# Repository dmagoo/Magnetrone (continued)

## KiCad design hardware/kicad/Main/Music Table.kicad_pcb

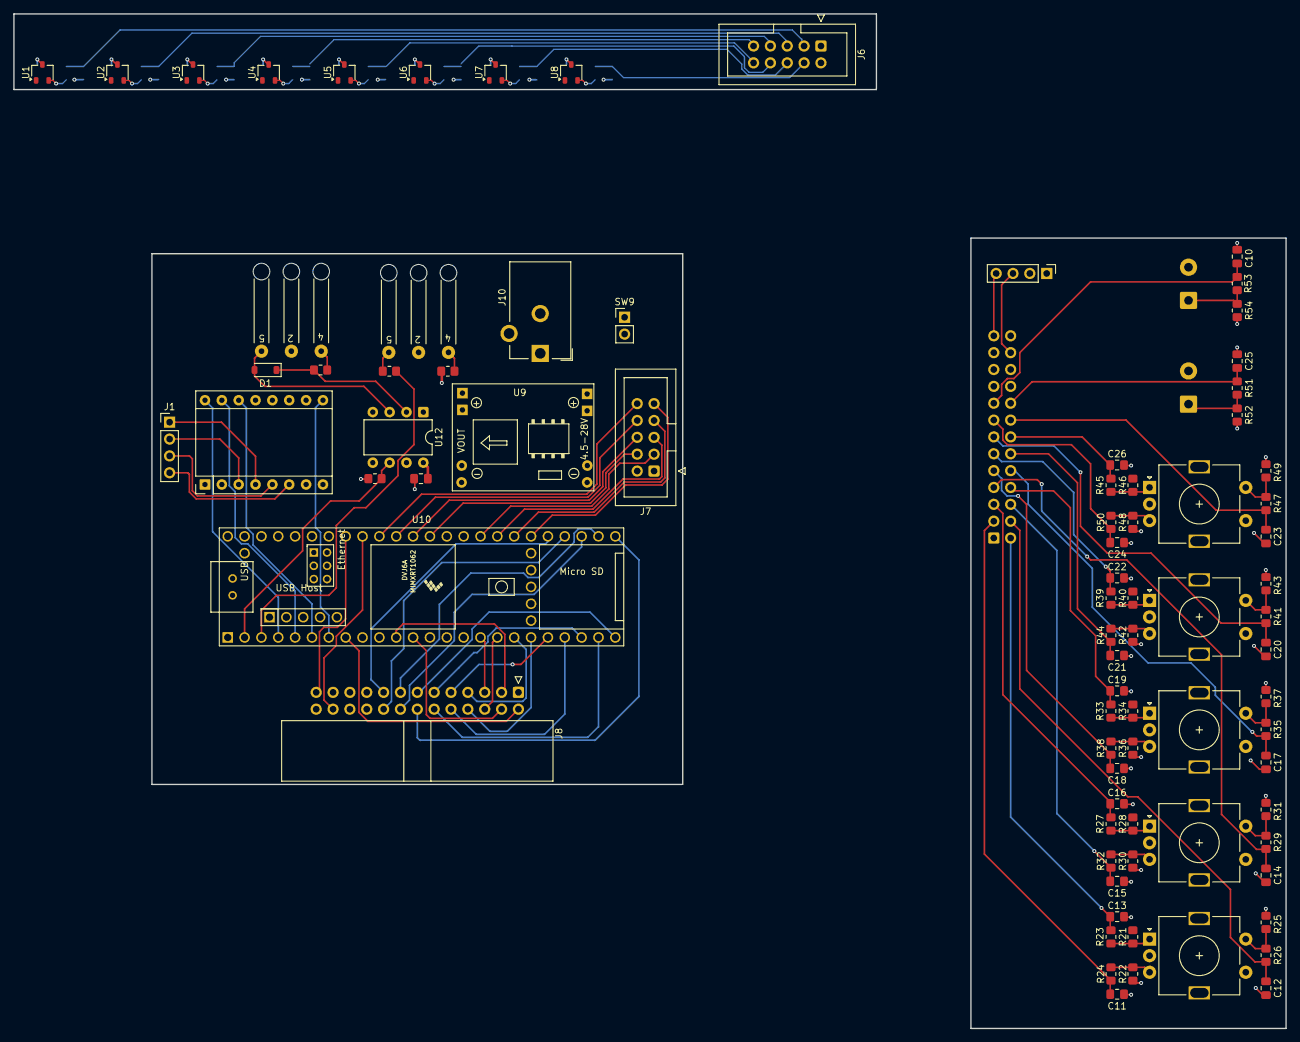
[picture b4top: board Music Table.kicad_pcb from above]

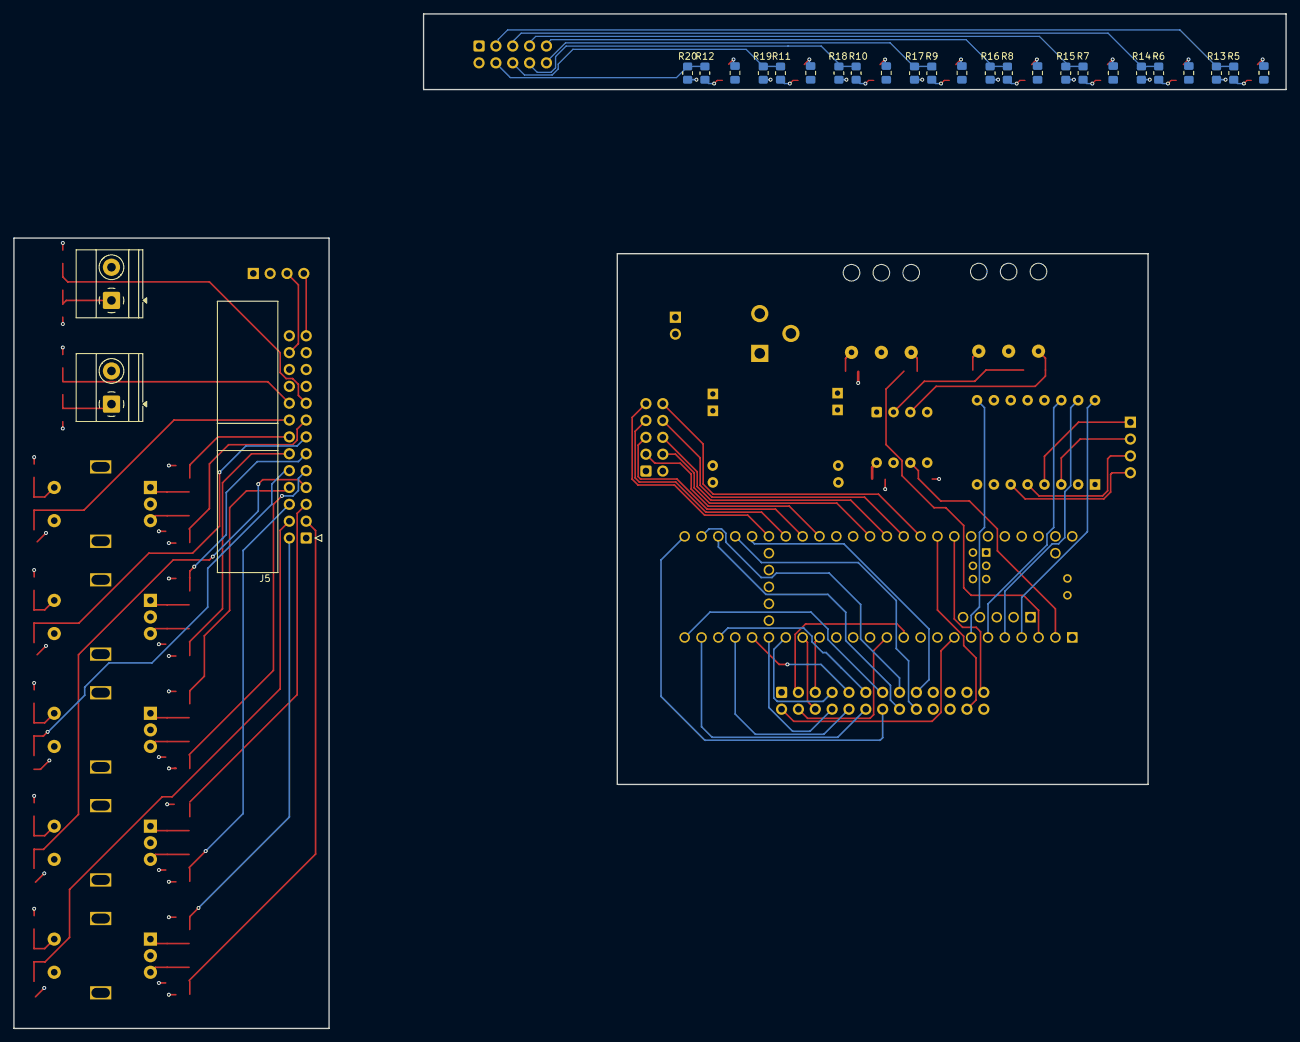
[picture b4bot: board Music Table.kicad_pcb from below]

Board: 4 copper layers, 191.7 x 152.9 mm, 110 parts (27 on the bottom side), 98 nets.

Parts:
A1: Pololu_Breakout_A4988; Pololu_Breakout-16_15.2x20.3mm
C1, C2, C3, C4, C5, C6, C7, C8, C9: .1uf; C_0805_2012Metric_Pad1.18x1.45mm_HandSolder
C10, C25: C; C_0805_2012Metric_Pad1.18x1.45mm_HandSolder
C11, C12, C13, C14, C15, C16, C17, C18, C19, C20, C21, C22, C23, C24, C26: .01uf; C_0805_2012Metric_Pad1.18x1.45mm_HandSolder
D1: D; D_SOD-123
J1, J9: Conn_01x04; PinHeader_1x04_P2.54mm_Vertical
J2, J3: DIN-5_180degree; MIDI_Wire_245
J5, J8: Conn_02x13_Counter_Clockwise; IDC-Header_2x13_P2.54mm_Horizontal
J6, J7: Conn_02x05_Odd_Even; IDC-Header_2x05_P2.54mm_Vertical
J10: Barrel_Jack; BarrelJack_CUI_PJ-102AH_Horizontal
R1, R2, R3: 220; R_0805_2012Metric_Pad1.20x1.40mm_HandSolder
R4: 470k; R_0805_2012Metric_Pad1.20x1.40mm_HandSolder
R5, R6, R7, R8, R9, R10, R11, R12: 10000; R_0805_2012Metric_Pad1.20x1.40mm_HandSolder
R13, R14, R15, R16, R17, R18, R19, R20: 20000; R_0805_2012Metric_Pad1.20x1.40mm_HandSolder
R21, R22, R23, R24, R25, R26, R27, R28, R29, R30, R31, R32, R33, R34, R35, R36, R37, R38, R39, R40, R41, R42, R43, R44, R45, R46, R47, R48, R49, R50: 10k; R_0805_2012Metric_Pad1.20x1.40mm_HandSolder
R51, R52, R53, R54: R; R_0805_2012Metric_Pad1.20x1.40mm_HandSolder
SW6, SW7: SW_Push; TerminalBlock_Phoenix_MKDS-1,5-2_1x02_P5.00mm_Horizontal
SW8, SW10, SW11, SW12, SW13: RotaryEncoder_Switch_MP; RotaryEncoder_Alps_EC11E-Switch_Vertical_H20mm
SW9: SW_SPST; PinHeader_1x02_P2.54mm_Vertical
U1, U2, U3, U4, U5, U6, U7, U8: A1301KLHLT-T; SOT-23W
U9: SRT_MPT1584EN_Module
U10: Teensy4.1; Teensy41
U12: 6N137; DIP-8_W7.62mm

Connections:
+3.3V: A1.2 (VDD), A1.13 (~RESET), C1.1, C2.1, C3.1, C4.1, C5.1, C6.1, C7.1, C8.1, J5.1, J6.1, J8.1, J9.2, R4.1, R21.1, R22.2, R25.2, R28.1, R30.2, R31.2, R34.1, R36.2, R37.2, R40.1, R42.2, R43.2, R46.1, R48.2, R49.2, R52.2, R54.1, U1.1 (VCC), U2.1 (VCC), U3.1 (VCC), U4.1 (VCC), U5.1 (VCC), U6.1 (VCC), U7.1 (VCC), U8.1 (VCC), U10.15 (3V3), U10.46 (3V3)
+5V: C9.2, J7.1, R2.2, U9.3 (VOUT), U10.48 (VIN), U12.8 (VCC)
+24V: A1.8 (VMOT), J10.1, SW9.1 (A), SW9.2 (B), U9.1 (VIN)
/Sensor Array/hall1: J6.3, R5.2, R13.2
/Sensor Array/hall2: J6.5, R6.2, R14.2
/Sensor Array/hall3: J6.7, R7.2, R15.2
/Sensor Array/hall4: J6.9, R8.2, R16.2
/Sensor Array/hall5: J6.10, R9.2, R17.2
/Sensor Array/hall6: J6.8, R10.2, R18.2
/Sensor Array/hall7: J6.6, R11.2, R19.2
/Sensor Array/hall8: J6.4, R12.2, R20.2
/mcu/aux1_btn: J8.18, U10.28 (36_CS)
/mcu/aux2_btn: J8.17, U10.29 (37_CS)
/mcu/encoder_aux1_a: J8.11, U10.22 (30_CRX3)
/mcu/encoder_aux1_b: J8.12, U10.23 (31_CTX3)
/mcu/encoder_aux1_btn: J8.13, U10.24 (32_OUT1B)
/mcu/encoder_aux2_a: J8.14, U10.25 (33_MCLK2)
/mcu/encoder_aux2_b: J8.15, U10.26 (34_RX8)
/mcu/encoder_aux2_btn: J8.16, U10.27 (35_TX8)
/mcu/hall1: J7.3, U10.33 (41_A17)
/mcu/hall2: J7.5, U10.32 (40_A16)
/mcu/hall3: J7.7, U10.31 (39_MISO1_OUT1A)
/mcu/hall4: J7.9, U10.30 (38_CS1_IN1)
/mcu/hall5: J7.10, U10.39 (17_A3_TX4_SDA1)
/mcu/hall6: J7.8, U10.38 (16_A2_RX4_SCL1)
/mcu/hall7: J7.6, U10.37 (15_A1_RX3_SPDIF_IN)
/mcu/hall8: J7.4, U10.36 (14_A0_TX3_SPDIF_OUT)
/mcu/menu_encoder_a: J8.2, U10.8 (6_OUT1D)
/mcu/menu_encoder_b: J8.3, U10.11 (9_OUT1C)
/mcu/menu_encoder_btn: J8.4, U10.12 (10_CS_MQSR)
/mcu/midi_rx: R4.2, U10.2 (0_RX1_CRX2_CS1), U12.6 (VO)
/mcu/midi_tx: R1.2, U10.3 (1_TX1_CTX2_MISO1)
/mcu/scl: J8.25, U10.41 (19_A5_SCL)
/mcu/sda: J8.24, U10.40 (18_A4_SDA)
/mcu/speed_encoder_a: J8.5, U10.16 (24_A10_TX6_SCL2)
/mcu/speed_encoder_b: J8.6, U10.17 (25_A11_RX6_SDA2)
/mcu/speed_encoder_btn: J8.7, U10.18 (26_A12_MOSI1)
/mcu/stepper_dir: A1.16 (DIR), U10.4 (2_OUT2)
/mcu/stepper_enable: A1.9 (~ENABLE), U10.7 (5_IN2)
/mcu/stepper_sleep: A1.14 (~SLEEP), U10.6 (4_BCLK2)
/mcu/stepper_step: A1.15 (STEP), U10.5 (3_LRCLK2)
/mcu/volume_encoder_a: J8.8, U10.19 (27_A13_SCK1)
/mcu/volume_encoder_b: J8.9, U10.20 (28_RX7)
/mcu/volume_encoder_btn: J8.10, U10.21 (29_TX7)
/ui/aux1_btn: C10.1, J5.17, R53.1
/ui/aux2_btn: C25.1, J5.18, R51.2
/ui/encoder_aux1_a: C22.1, J5.11, R39.2
/ui/encoder_aux1_b: C21.1, J5.12, R44.2
/ui/encoder_aux1_btn: C20.1, J5.13, R41.2
/ui/encoder_aux2_a: C26.1, J5.14, R45.2
/ui/encoder_aux2_b: C24.1, J5.15, R50.2
/ui/encoder_aux2_btn: C23.1, J5.16, R47.2
/ui/menu_encoder_a: C13.1, J5.2, R23.2
/ui/menu_encoder_b: C11.1, J5.3, R24.2
/ui/menu_encoder_btn: C12.1, J5.4, R26.2
/ui/scl: J5.25, J9.4
/ui/sda: J5.24, J9.3
/ui/speed_encoder_a: C16.1, J5.5, R27.2
/ui/speed_encoder_b: C15.1, J5.6, R32.2
/ui/speed_encoder_btn: C14.1, J5.7, R29.2
/ui/volume_encoder_a: C19.1, J5.8, R33.2
/ui/volume_encoder_b: C18.1, J5.9, R38.2
/ui/volume_encoder_btn: C17.1, J5.10, R35.2
GND: A1.1 (GND), A1.7 (GND), C1.2, C2.2, C3.2, C4.2, C5.2, C6.2, C7.2, C8.2, C9.1, C10.2, C11.2, C12.2, C13.2, C14.2, C15.2, C16.2, C17.2, C18.2, C19.2, C20.2, C21.2, C22.2, C23.2, C24.2, C25.2, C26.2, J5.26, J6.2, J7.2, J8.26, J9.1, J10.2, R13.1, R14.1, R15.1, R16.1, R17.1, R18.1, R19.1, R20.1, SW6.2, SW7.2, SW8.C, SW8.MP, SW8.S1, SW10.C, SW10.MP, SW10.S1, SW11.C, SW11.MP, SW11.S1, SW12.C, SW12.MP, SW12.S1, SW13.C, SW13.MP, SW13.S1, U1.3 (GND), U2.3 (GND), U3.3 (GND), U4.3 (GND), U5.3 (GND), U6.3 (GND), U7.3 (GND), U8.3 (GND), U9.2 (GND), U9.4 (GND), U10.1 (GND), U10.34 (GND), U10.47 (GND), U12.5 (GND)
unnamed: A1.4 (1A), J1.1
unnamed: A1.3 (1B), J1.2
unnamed: A1.5 (2A), J1.3
unnamed: A1.6 (2B), J1.4
unnamed: D1.2 (A), J3.5, U12.3 (C)
unnamed: D1.1 (K), R3.2, U12.2 (A)
unnamed: J2.4, R2.1
unnamed: J2.5, R1.1
unnamed: J3.4, R3.1
unnamed: R21.2, R23.1, SW8.A
unnamed: R22.1, R24.1, SW8.B
unnamed: R25.1, R26.1, SW8.S2
unnamed: R27.1, R28.2, SW10.A
unnamed: R29.1, R31.1, SW10.S2
unnamed: R30.1, R32.1, SW10.B
unnamed: R33.1, R34.2, SW11.A
unnamed: R35.1, R37.1, SW11.S2
unnamed: R36.1, R38.1, SW11.B
unnamed: R39.1, R40.2, SW12.A
unnamed: R41.1, R43.1, SW12.S2
unnamed: R42.1, R44.1, SW12.B
unnamed: R45.1, R46.2, SW13.A
unnamed: R47.1, R49.1, SW13.S2
unnamed: R48.1, R50.1, SW13.B
unnamed: R51.1, R52.1, SW6.1
unnamed: R53.2, R54.2, SW7.1
unnamed: R5.1, U1.2 (VOUT)
unnamed: R6.1, U2.2 (VOUT)
unnamed: R7.1, U3.2 (VOUT)
unnamed: R8.1, U4.2 (VOUT)
unnamed: R9.1, U5.2 (VOUT)
unnamed: R10.1, U6.2 (VOUT)
unnamed: R11.1, U7.2 (VOUT)
unnamed: R12.1, U8.2 (VOUT)

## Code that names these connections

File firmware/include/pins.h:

#pragma once
// All pin numbers are GPIO numbers (Teensy 4.1 Arduino API).

// MIDI
constexpr int PIN_MIDI_RX       = 0;
constexpr int PIN_MIDI_TX       = 1;

// Stepper driver (TMC2209)
constexpr int PIN_DIR           = 2;
constexpr int PIN_DIR_TMP       = 6;    // used for testing as there was a broken teensy pin
constexpr int PIN_STEP          = 3;
constexpr int PIN_ENABLE        = 5;    // stepper_enable

// TMC2209 UART (Serial8)
constexpr int PIN_STEPPER_RX   = 34;
constexpr int PIN_STEPPER_TX   = 35;



// Menu encoder
constexpr int PIN_MENU_A        = 6;
constexpr int PIN_MENU_B        = 9;
constexpr int PIN_MENU_BTN      = 10;

// Speed encoder
constexpr int PIN_SPEED_A       = 24;
constexpr int PIN_SPEED_B       = 25;
constexpr int PIN_SPEED_BTN     = 37;  // press = stop/resume

// Volume encoderG
constexpr int PIN_VOL_A         = 29;
constexpr int PIN_VOL_B         = 27;
constexpr int PIN_VOL_BTN       = 28;  // press = mute/unmute

// Aux encoder 1 (reserved)
constexpr int PIN_AUX_ENC_A     = 30;
constexpr int PIN_AUX_ENC_B     = 31;
constexpr int PIN_AUX_ENC_BTN   = 32;

// Aux button (reserved)
constexpr int PIN_AUX_BTN_1     = 36;

// Hall effect sensors
constexpr int PIN_HALL_1        = 17;
constexpr int PIN_HALL_2        = 14;
constexpr int PIN_HALL_3        = 39;
constexpr int PIN_HALL_4        = 38;
constexpr int PIN_HALL_5        = 40;
constexpr int PIN_HALL_6        = 41;
constexpr int PIN_HALL_7        = 16;
constexpr int PIN_HALL_8        = 26;

// I2C - shared bus (LCD + audio shield SGTL5000)
constexpr int PIN_SDA           = 18;
constexpr int PIN_SCL           = 19;

// Audio shield I2S - managed by Teensy Audio Library, defined here for reference only.
// T4.1: MCLK=23, BCLK=21, LRCLK=20, DOUT=7, DIN(rx)=8
// Pins 7, 8, 20, 21, 23 are driven by the audio shield - do not connect or use.

// SD card SPI (reserved, not implemented)
// Pin 12: SPI MISO - do not use if external SD fitted

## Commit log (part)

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2026-06-05 initial import: music table kicad, firmware, notes
2026-06-06 feat: break into multiple boards
2026-06-07 chore: cleanup
2026-06-07 feat: cleanup
2026-06-07 sensor step
2026-06-09 feat: updates
2026-06-09 feat: update to 2 layer board
2026-06-09 chore: cleanup/mounting holes
2026-06-10 chore: tests
2026-06-13 chore: rename project files
2026-06-15 chore: test for new motor driver
2026-06-15 chore: replace motor driver
